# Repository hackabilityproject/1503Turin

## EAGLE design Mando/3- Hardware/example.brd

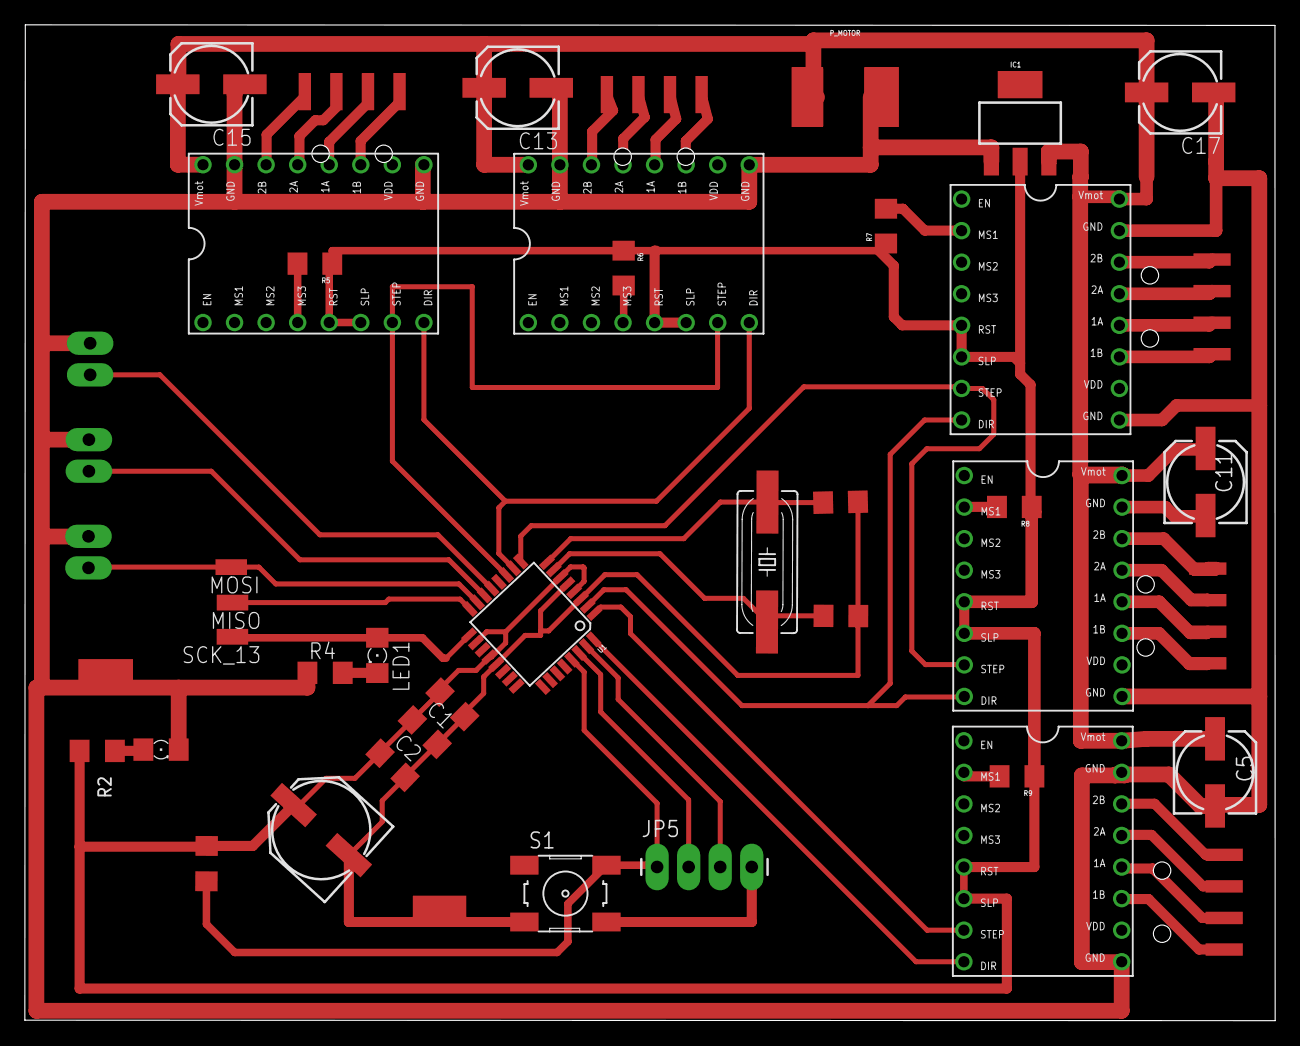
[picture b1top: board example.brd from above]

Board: 2 copper layers, 100.6 x 80.1 mm, 43 parts (0 on the bottom side), 47 nets.

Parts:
C1: 100n; C1206
C2: 10u; C1206
C3: 100uF; PANASONIC_E
C5, C11, C13, C15, C17: 47uF; 153CLV-0605
C6: 1u; C1206
C7, C8: 22p; C1206
IC1: SOT223
JP1, JP2, JP3, JP4, JP9: 1X04-SMD
JP5: 1X04_LONGPADS
LED1: 1206
LED_PWR: 1206
MISO: SMD1,27-2,54
MOSI: SMD1,27-2,54
P_MOTOR: S2B-PH
Q1: 16MHz; SM49
R1: 10k; R1206
R2: 1k; R1206
R4: R1206
R5, R6, R7, R8, R9: 1206
S1: 6MM_SWITCH
SCK_13: SMD1,27-2,54
U1: ATMEGA168; TQFP32-08
XAXIS: A4988BREAKOUT
XLIMIT: 1X02_LONGPADS
YAXIS1, YAXIS2: A4988BREAKOUT
YLIMIT: 1X02_LONGPADS
ZAXIS1, ZAXIS2: A4988BREAKOUT
ZLIMIT: 1X02_LONGPADS

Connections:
2: U1.32, XAXIS.DIR
3: U1.1, XAXIS.STEP
4: U1.2, YAXIS1.DIR, YAXIS2.DIR
5: U1.9, YAXIS1.STEP, YAXIS2.STEP
6: U1.10, ZAXIS1.DIR, ZAXIS2.DIR
7: U1.11, ZAXIS1.STEP, ZAXIS2.STEP
9: U1.13, XLIMIT.1
10: U1.14, YLIMIT.1
GND: C1.2, C2.2, C3.-, C5.-, C6.2, C7.1, C8.1, C11.-, C13.-, C15.-, C17.-, IC1.1, JP5.4, LED_PWR.C, P_MOTOR.2, R4.1, S1.3, S1.4, U1.3, U1.5, U1.21, XAXIS.GND, XAXIS.GND@0, XLIMIT.2, YAXIS1.GND, YAXIS1.GND@0, YAXIS2.GND, YAXIS2.GND@0, YLIMIT.2, ZAXIS1.GND, ZAXIS1.GND@0, ZAXIS2.GND, ZAXIS2.GND@0, ZLIMIT.2
MISO_12: MISO.1, U1.16
MOSI_11: MOSI.1, U1.15, ZLIMIT.1
unnamed: LED_PWR.A, R2.2
unnamed: R7.2, YAXIS2.MS1
unnamed: JP1.2, ZAXIS2.2A
unnamed: JP1.1, ZAXIS2.2B
unnamed: LED1.C, R4.2
unnamed: JP1.3, ZAXIS2.1A
unnamed: JP2.1, XAXIS.2B
unnamed: JP2.2, XAXIS.2A
unnamed: JP2.3, XAXIS.1A
unnamed: JP2.4, XAXIS.1B
unnamed: JP1.4, ZAXIS2.1B
unnamed: JP3.2, YAXIS2.2A
unnamed: JP4.2, YAXIS1.2A
unnamed: JP4.1, YAXIS1.2B
unnamed: JP4.3, YAXIS1.1A
unnamed: JP4.4, YAXIS1.1B
unnamed: JP3.1, YAXIS2.2B
unnamed: JP3.3, YAXIS2.1A
unnamed: JP3.4, YAXIS2.1B
unnamed: JP9.2, ZAXIS1.2A
unnamed: JP9.1, ZAXIS1.2B
unnamed: R5.2, ZAXIS2.MS3
unnamed: JP9.3, ZAXIS1.1A
unnamed: JP9.4, ZAXIS1.1B
unnamed: R6.2, ZAXIS1.MS3
unnamed: R8.2, YAXIS1.MS1
unnamed: R9.2, XAXIS.MS1
RESET: JP5.1, R1.1, S1.1, S1.2, U1.29
RX: JP5.3, U1.31
SCK_13: LED1.A, SCK_13.1, U1.17
TX: JP5.2, U1.30
VCC: C1.1, C2.1, C3.+, C6.1, IC1.2, R1.2, R2.1, R5.1, R6.1, R7.1, R8.1, R9.1, U1.4, U1.6, U1.18, U1.20, XAXIS.RST, XAXIS.SLP, YAXIS1.RST, YAXIS1.SLP, YAXIS2.RST, YAXIS2.SLP, ZAXIS1.RST, ZAXIS1.SLP, ZAXIS2.RST, ZAXIS2.SLP
VDD: XAXIS.VDD, YAXIS1.VDD, YAXIS2.VDD, ZAXIS1.VDD, ZAXIS2.VDD
VMOT: C5.+, C11.+, C13.+, C15.+, C17.+, IC1.3, P_MOTOR.1, XAXIS.VMOT, YAXIS1.VMOT, YAXIS2.VMOT, ZAXIS1.VMOT, ZAXIS2.VMOT
XTAL1: C8.2, Q1.2, U1.7
XTAL2: C7.2, Q1.1, U1.8

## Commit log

2015-07-27 added to do list for documentation
2015-08-24 aggiunto DiCulo
2017-01-23 aggiunto pdf di taglio di diculo

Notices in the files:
parts and their libraries:
SparkFun-Connectors: Licensing: CC v3.0 Share-Alike You are welcome to use this library for commercial purposes.
